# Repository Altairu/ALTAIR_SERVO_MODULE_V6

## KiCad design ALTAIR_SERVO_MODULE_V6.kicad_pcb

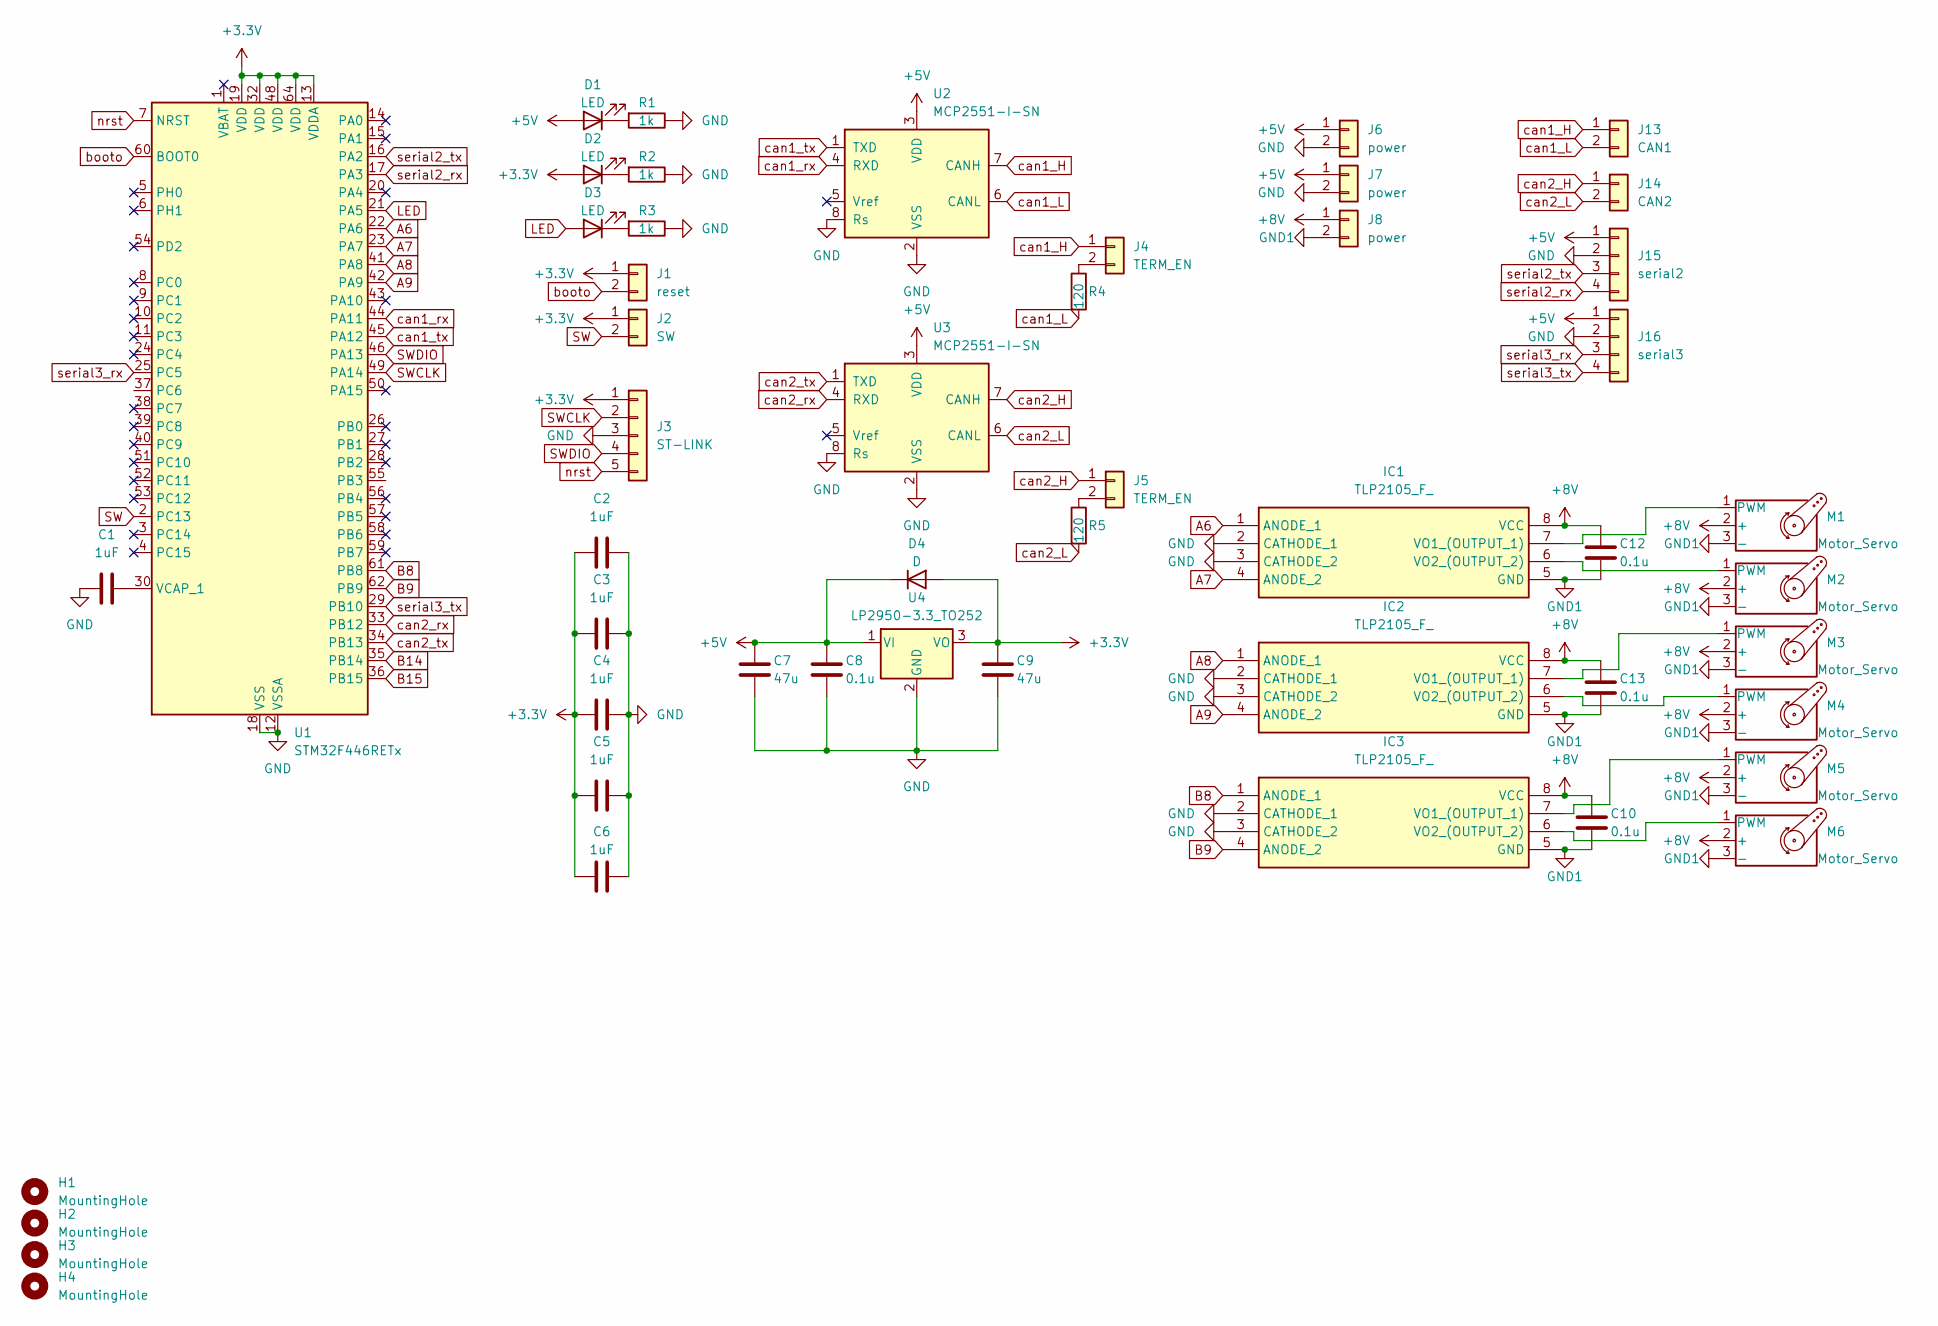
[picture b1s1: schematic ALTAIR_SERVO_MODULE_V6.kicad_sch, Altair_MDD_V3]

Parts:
C1, C2, C3, C4, C5, C6: 1uF; C_0603_1608Metric
C7, C9: 47u; C_0603_1608Metric
C8, C10, C12, C13: 0.1u; C_0603_1608Metric
D1, D2, D3: LED; LED_0603_1608Metric
D4: D; D_0603_1608Metric
H1, H2, H3, H4: MountingHole; MountingHole_3.2mm_M3_Pad_Via
IC1, IC2, IC3: TLP2105_F_; TLP2105; Manufacturer_Part_Number TLP2105(F); Mouser Part Number 757-TLP2105(F)
J1: reset; PinSocket_1x02_P2.54mm_Vertical
J2: SW; PinSocket_1x02_P2.54mm_Vertical
J3: ST-LINK; PinSocket_1x05_P2.54mm_Vertical
J4, J5: TERM_EN; PinSocket_1x02_P2.54mm_Vertical
J6, J7: power; JST_XA_S02B-XASK-1_1x02_P2.50mm_Horizontal
J8: power; AMASS_XT30PW-M_1x02_P2.50mm_Horizontal
J13: CAN1; JST_XA_S02B-XASK-1_1x02_P2.50mm_Horizontal
J14: CAN2; JST_XA_S02B-XASK-1_1x02_P2.50mm_Horizontal
J15: serial2; JST_XA_B04B-XASK-1-A_1x04_P2.50mm_Vertical
J16: serial3; JST_XA_B04B-XASK-1-A_1x04_P2.50mm_Vertical
M1, M2, M3, M4, M5, M6: Motor_Servo; JST_XA_S03B-XASK-1_1x03_P2.50mm_Horizontal
R1, R2, R3: 1k; R_0603_1608Metric
R4, R5: 120; R_0603_1608Metric
U1: STM32F446RETx; LQFP-64_10x10mm_P0.5mm
U2, U3: MCP2551-I-SN; SOIC-8_3.9x4.9mm_P1.27mm
U4: LP2950-3.3_TO252; TO-252-2

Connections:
+3.3V: C2.1, C3.1, C4.1, C5.1, C6.1, C9.1, D2.2 (A), D4.2 (A), J1.1, J2.1, J3.1, U1.13 (VDDA), U1.19 (VDD), U1.32 (VDD), U1.48 (VDD), U1.64 (VDD), U4.3 (VO)
+5V: C7.1, C8.1, D1.2 (A), D4.1 (K), J6.1, J7.1, J15.1, J16.1, U2.3 (VDD), U3.3 (VDD), U4.1 (VI)
+8V: C10.1, C12.1, C13.1, IC1.8 (VCC), IC2.8 (VCC), IC3.8 (VCC), J8.1, M1.2 (+), M2.2 (+), M3.2 (+), M4.2 (+), M5.2 (+), M6.2 (+)
A6: IC1.1 (ANODE_1), U1.22 (PA6)
A7: IC1.4 (ANODE_2), U1.23 (PA7)
A8: IC2.1 (ANODE_1), U1.41 (PA8)
A9: IC2.4 (ANODE_2), U1.42 (PA9)
B8: IC3.1 (ANODE_1), U1.61 (PB8)
B9: IC3.4 (ANODE_2), U1.62 (PB9)
B14: U1.35 (PB14)
B15: U1.36 (PB15)
GND: C1.1, C2.2, C3.2, C4.2, C5.2, C6.2, C7.2, C8.2, C9.2, IC1.2 (CATHODE_1), IC1.3 (CATHODE_2), IC2.2 (CATHODE_1), IC2.3 (CATHODE_2), IC3.2 (CATHODE_1), IC3.3 (CATHODE_2), J3.3, J6.2, J7.2, J15.2, J16.2, R1.1, R2.1, R3.1, U1.12 (VSSA), U1.18 (VSS), U1.31 (VSS), U1.47 (VSS), U1.63 (VSS), U2.2 (VSS), U2.8 (Rs), U3.2 (VSS), U3.8 (Rs), U4.2 (GND)
GND1: C10.2, C12.2, C13.2, IC1.5 (GND), IC2.5 (GND), IC3.5 (GND), J8.2, M1.3 (-), M2.3 (-), M3.3 (-), M4.3 (-), M5.3 (-), M6.3 (-)
LED: D3.2 (A), U1.21 (PA5)
unnamed: D1.1 (K), R1.2
unnamed: D2.1 (K), R2.2
unnamed: D3.1 (K), R3.2
unnamed: IC1.7 (VO1_(OUTPUT_1)), M1.1 (PWM)
unnamed: IC1.6 (VO2_(OUTPUT_2)), M2.1 (PWM)
unnamed: IC2.7 (VO1_(OUTPUT_1)), M3.1 (PWM)
unnamed: IC2.6 (VO2_(OUTPUT_2)), M4.1 (PWM)
unnamed: IC3.7 (VO1_(OUTPUT_1)), M5.1 (PWM)
unnamed: IC3.6 (VO2_(OUTPUT_2)), M6.1 (PWM)
unnamed: J4.2, R4.1
unnamed: J5.2, R5.1
unnamed: C1.2, U1.30 (VCAP_1)
SW: J2.2, U1.2 (PC13)
SWCLK: J3.2, U1.49 (PA14)
SWDIO: J3.4, U1.46 (PA13)
booto: J1.2, U1.60 (BOOT0)
can1_H: J4.1, J13.1, U2.7 (CANH)
can1_L: J13.2, R4.2, U2.6 (CANL)
can1_rx: U1.44 (PA11), U2.4 (RXD)
can1_tx: U1.45 (PA12), U2.1 (TXD)
can2_H: J5.1, J14.1, U3.7 (CANH)
can2_L: J14.2, R5.2, U3.6 (CANL)
can2_rx: U1.33 (PB12), U3.4 (RXD)
can2_tx: U1.34 (PB13), U3.1 (TXD)
nrst: J3.5, U1.7 (NRST)
serial2_rx: J15.4, U1.17 (PA3)
serial2_tx: J15.3, U1.16 (PA2)
serial3_rx: J16.3, U1.25 (PC5)
serial3_tx: J16.4, U1.29 (PB10)

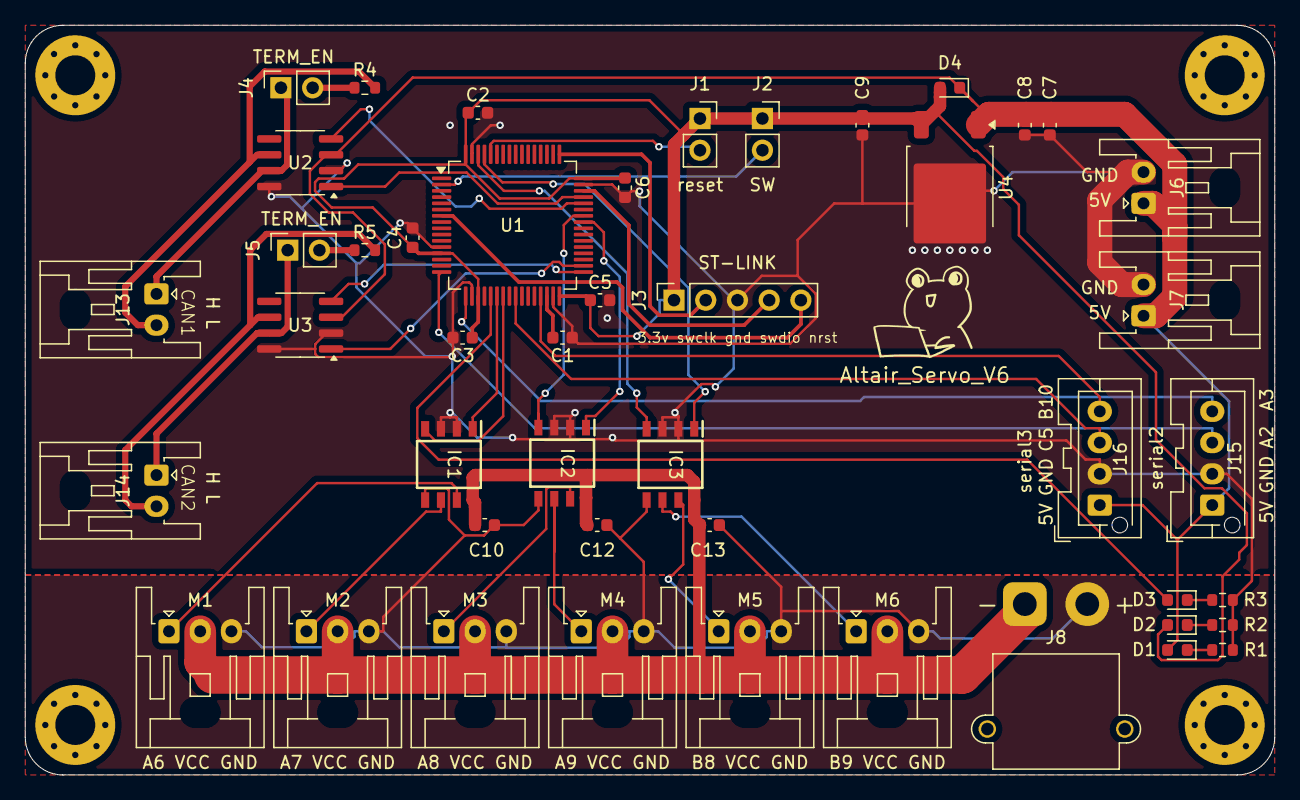
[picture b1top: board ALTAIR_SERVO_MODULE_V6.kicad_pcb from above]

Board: 2 copper layers, 100.0 x 60.0 mm, 50 parts (0 on the bottom side), 41 nets.

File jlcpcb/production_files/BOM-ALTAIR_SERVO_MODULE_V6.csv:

Comment,Designator,Footprint,LCSC,Quantity
0.1u,"C10,C12,C13,C8",C_0603_1608Metric,C125205,4
LP2950-3.3_TO252,U4,TO-252-2,C129994,1
47u,"C7,C9",C_0603_1608Metric,C140782,2
120,"R4,R5",R_0603_1608Metric,C14709,2
1uF,"C1,C2,C3,C4,C5,C6",C_0603_1608Metric,C1592,6
LED,"D1,D2,D3",LED_0603_1608Metric,C2290,3
TLP2105_F_,"IC1,IC2,IC3",TLP2105,C2880451,3
D,D4,D_0603_1608Metric,C3758192,1
STM32F446RETx,U1,LQFP-64_10x10mm_P0.5mm,C69336,1
MCP2551-I-SN,"U2,U3",SOIC-8_3.9x4.9mm_P1.27mm,C7376,2
1k,"R1,R2,R3",R_0603_1608Metric,C78748,3
Motor_Servo,M1,JST_XA_S03B-XASK-1_1x03_P2.50mm_Horizontal,,1
SW,J2,PinSocket_1x02_P2.54mm_Vertical,,1
power,J6,JST_XA_S02B-XASK-1_1x02_P2.50mm_Horizontal,,1
MountingHole,H2,MountingHole_3.2mm_M3_Pad_Via,,1
serial2,J15,JST_XA_B04B-XASK-1-A_1x04_P2.50mm_Vertical,,1
Motor_Servo,M5,JST_XA_S03B-XASK-1_1x03_P2.50mm_Horizontal,,1
TERM_EN,J4,PinSocket_1x02_P2.54mm_Vertical,,1
power,J8,AMASS_XT30PW-M_1x02_P2.50mm_Horizontal,,1
Motor_Servo,M2,JST_XA_S03B-XASK-1_1x03_P2.50mm_Horizontal,,1
serial3,J16,JST_XA_B04B-XASK-1-A_1x04_P2.50mm_Vertical,,1
reset,J1,PinSocket_1x02_P2.54mm_Vertical,,1
MountingHole,H1,MountingHole_3.2mm_M3_Pad_Via,,1
TERM_EN,J5,PinSocket_1x02_P2.54mm_Vertical,,1
Motor_Servo,M4,JST_XA_S03B-XASK-1_1x03_P2.50mm_Horizontal,,1
MountingHole,H4,MountingHole_3.2mm_M3_Pad_Via,,1
CAN2,J14,JST_XA_S02B-XASK-1_1x02_P2.50mm_Horizontal,,1
Motor_Servo,M3,JST_XA_S03B-XASK-1_1x03_P2.50mm_Horizontal,,1
ST-LINK,J3,PinSocket_1x05_P2.54mm_Vertical,,1
CAN1,J13,JST_XA_S02B-XASK-1_1x02_P2.50mm_Horizontal,,1
Motor_Servo,M6,JST_XA_S03B-XASK-1_1x03_P2.50mm_Horizontal,,1
power,J7,JST_XA_S02B-XASK-1_1x02_P2.50mm_Horizontal,,1
MountingHole,H3,MountingHole_3.2mm_M3_Pad_Via,,1
